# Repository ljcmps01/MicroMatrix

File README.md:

# MicroMatrix
Proyecto de matriz miniatura 8x8 controlado con STM32F051 utilizando multiplexacion

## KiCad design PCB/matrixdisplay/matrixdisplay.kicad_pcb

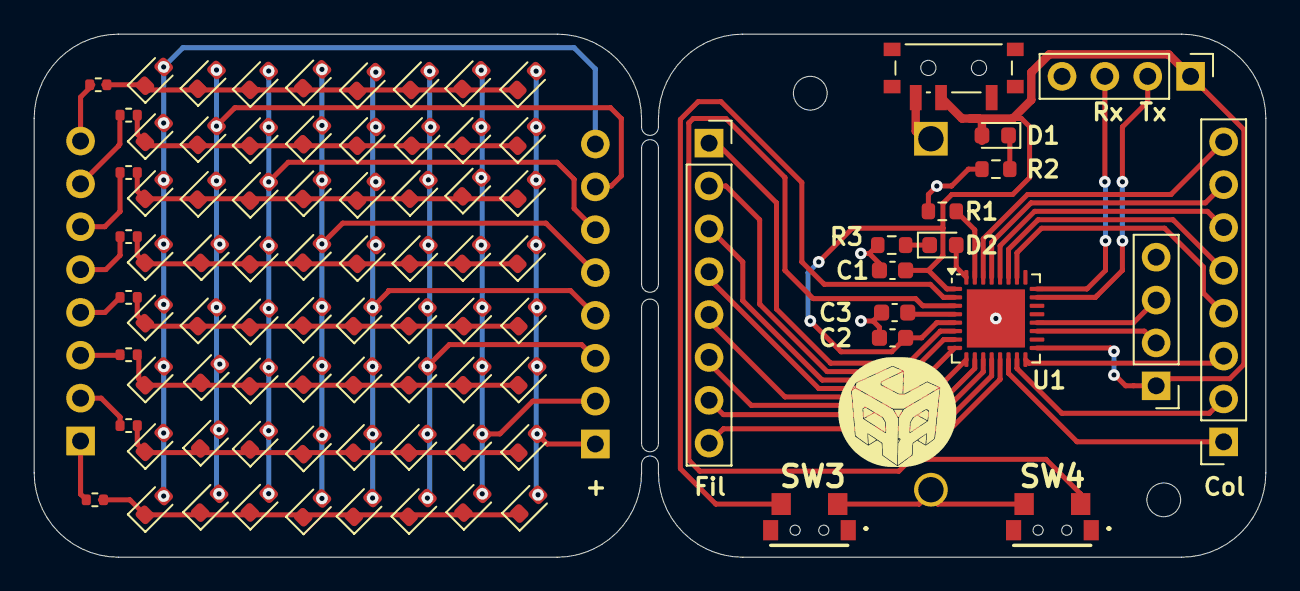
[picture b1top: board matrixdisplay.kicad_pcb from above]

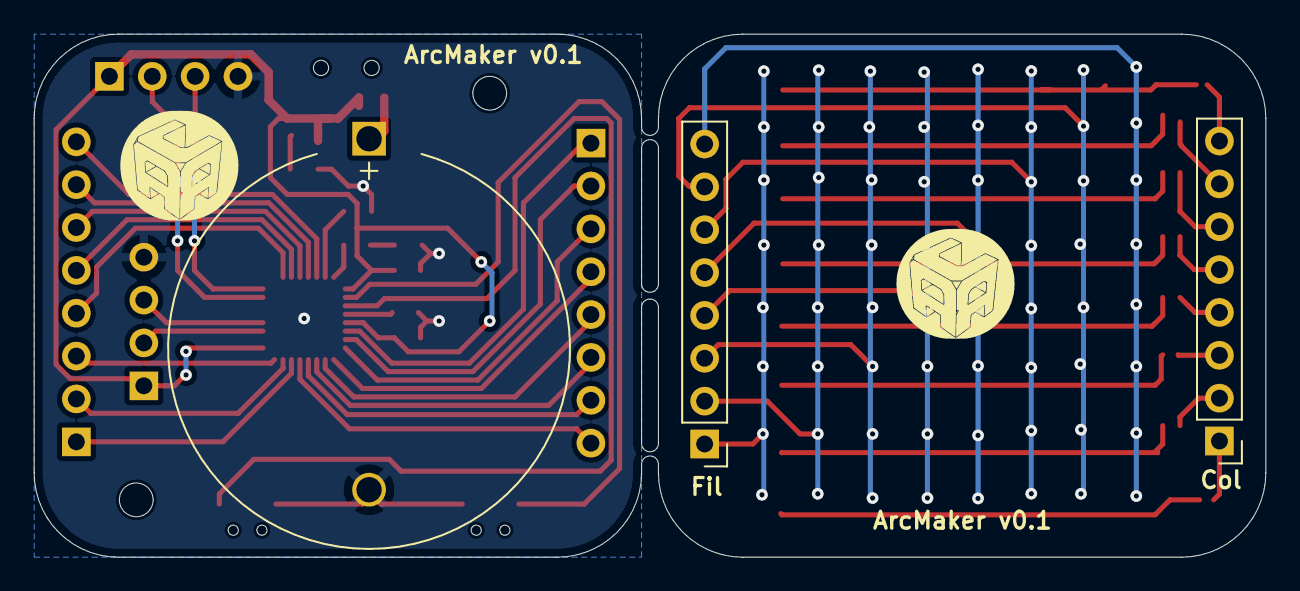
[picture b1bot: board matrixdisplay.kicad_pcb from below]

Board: 2 copper layers, 73.0 x 31.0 mm, 93 parts (3 on the bottom side), 54 nets.

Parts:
BT1: CR2032; BatteryHolder_MYOUNG_BS-07-A1BJ001_CR2032
C1, C2, C3: 100n; C_0603_1608Metric
D1, D2, D3, D4, D5, D6, D7, D8, D9, D10, D11, D12, D13, D14, D15, D16, D17, D18, D19, D20, D21, D22, D23, D24, D25, D26, D27, D28, D29, D30, D31, D32, D33, D34, D35, D36, D37, D38, D39, D40, D41, D42, D43, D44, D45, D46, D47, D48, D49, D50, D51, D52, D53, D54, D55, D56, D57, D58, D59, D60, D61, D62, D63, D64, D65, D66: LED; LED_0603_1608Metric
H1, H2: MountingHole; MountingHole_2mm
J1: FILAS; PinSocket_1x08_P2.54mm_Vertical
J2: COLUMNAS; PinSocket_1x08_P2.54mm_Vertical
J3: SWD; PinHeader_1x04_P2.54mm_Vertical
J4: USART; PinHeader_1x04_P2.54mm_Vertical
J5: FILAS; PinHeader_1x08_P2.54mm_Vertical
J6: COL; PinHeader_1x08_P2.54mm_Vertical
R1: 10k; R_0603_1608Metric
R2: 220; R_0603_1608Metric
R3: 120; R_0603_1608Metric
R4, R5, R6, R7, R8, R9, R10, R11: 220; R_0402_1005Metric
SW2: P_ON; SW_SPDT_PCM12
SW3: BT1; TS24CA
SW4: BT2; TS24CA
U1: STM32F051K8Ux; QFN-32-1EP_5x5mm_P0.5mm_EP3.45x3.45mm

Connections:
+3.3V: C1.1, C2.1, D1.2 (A), J3.1, J4.1, SW2.2 (B), U1.1 (VDD), U1.5 (VDDA), U1.17 (VDD)
GND: BT1.2 (-), C1.2, C2.2, C3.2, J3.4, J4.4, R1.1, R2.2, R3.1, SW3.2, SW4.2, U1.33 (VSS)
unnamed: BT1.1 (+), SW2.3 (C)
unnamed: D1.1 (K), R2.1
unnamed: D2.2 (A), U1.32 (PB8)
unnamed: D2.1 (K), R3.2
unnamed: D3.2 (A), D4.2 (A), D5.2 (A), D6.2 (A), D7.2 (A), D8.2 (A), D9.2 (A), D10.2 (A), J5.8
unnamed: D10.1 (K), D18.1 (K), D26.1 (K), D34.1 (K), D63.1 (K), D64.1 (K), D65.1 (K), D66.1 (K), R4.2
unnamed: D11.2 (A), D12.2 (A), D13.2 (A), D14.2 (A), D15.2 (A), D16.2 (A), D17.2 (A), D18.2 (A), J5.7
unnamed: D3.1 (K), D11.1 (K), D19.1 (K), D27.1 (K), D35.1 (K), D36.1 (K), D37.1 (K), D38.1 (K), R11.1
unnamed: D4.1 (K), D12.1 (K), D20.1 (K), D28.1 (K), D39.1 (K), D40.1 (K), D41.1 (K), D42.1 (K), R10.1
unnamed: D5.1 (K), D13.1 (K), D21.1 (K), D29.1 (K), D43.1 (K), D44.1 (K), D45.1 (K), D46.1 (K), R9.1
unnamed: D6.1 (K), D14.1 (K), D22.1 (K), D30.1 (K), D47.1 (K), D48.1 (K), D49.1 (K), D50.1 (K), R8.1
unnamed: D7.1 (K), D15.1 (K), D23.1 (K), D31.1 (K), D51.1 (K), D52.1 (K), D53.1 (K), D54.1 (K), R7.2
unnamed: D8.1 (K), D16.1 (K), D24.1 (K), D32.1 (K), D55.1 (K), D56.1 (K), D57.1 (K), D58.1 (K), R6.2
unnamed: D9.1 (K), D17.1 (K), D25.1 (K), D33.1 (K), D59.1 (K), D60.1 (K), D61.1 (K), D62.1 (K), R5.2
unnamed: D19.2 (A), D20.2 (A), D21.2 (A), D22.2 (A), D23.2 (A), D24.2 (A), D25.2 (A), D26.2 (A), J5.6
unnamed: D27.2 (A), D28.2 (A), D29.2 (A), D30.2 (A), D31.2 (A), D32.2 (A), D33.2 (A), D34.2 (A), J5.5
unnamed: D35.2 (A), D39.2 (A), D43.2 (A), D47.2 (A), D51.2 (A), D55.2 (A), D59.2 (A), D63.2 (A), J5.4
unnamed: D36.2 (A), D40.2 (A), D44.2 (A), D48.2 (A), D52.2 (A), D56.2 (A), D60.2 (A), D64.2 (A), J5.3
unnamed: D37.2 (A), D41.2 (A), D45.2 (A), D49.2 (A), D53.2 (A), D57.2 (A), D61.2 (A), D65.2 (A), J5.2
unnamed: D38.2 (A), D42.2 (A), D46.2 (A), D50.2 (A), D54.2 (A), D58.2 (A), D62.2 (A), D66.2 (A), J5.1
unnamed: J1.1, U1.6 (PA0)
unnamed: J1.2, U1.7 (PA1)
unnamed: J1.3, U1.8 (PA2)
unnamed: J1.4, U1.9 (PA3)
unnamed: J1.5, U1.10 (PA4)
unnamed: J1.6, U1.11 (PA5)
unnamed: J1.7, U1.12 (PA6)
unnamed: J1.8, U1.13 (PA7)
unnamed: J2.1, U1.14 (PB0)
unnamed: J2.2, U1.15 (PB1)
unnamed: J2.3, U1.16 (PB2)
unnamed: J2.4, U1.26 (PB3)
unnamed: J2.5, U1.27 (PB4)
unnamed: J2.6, U1.28 (PB5)
unnamed: J2.7, U1.29 (PB6)
unnamed: J2.8, U1.30 (PB7)
unnamed: J3.2, U1.23 (PA13)
unnamed: J3.3, U1.24 (PA14)
unnamed: J4.2, U1.19 (PA9)
unnamed: J4.3, U1.20 (PA10)
unnamed: J6.1, R4.1
unnamed: J6.2, R5.1
unnamed: J6.3, R6.1
unnamed: J6.4, R7.1
unnamed: J6.5, R8.2
unnamed: J6.6, R9.2
unnamed: J6.7, R10.2
unnamed: J6.8, R11.2
unnamed: R1.2, U1.31 (BOOT0)
unnamed: C3.1, U1.4 (NRST)
unnamed: SW3.1, U1.2 (PF0)
unnamed: SW4.1, U1.3 (PF1)

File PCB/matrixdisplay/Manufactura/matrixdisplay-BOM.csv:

"Reference","Value","Datasheet","Footprint","Qty","DNP"
"BT1","CR2032","~","Battery:BatteryHolder_MYOUNG_BS-07-A1BJ001_CR2032","1",""
"C1,C2,C3","100n","~","Capacitor_SMD:C_0603_1608Metric","3",""
"D1,D2,D3,D4,D5,D6,D7,D8,D9,D10,D11,D12,D13,D14,D15,D16,D17,D18,D19,D20,D21,D22,D23,D24,D25,D26,D27,D28,D29,D30,D31,D32,D33,D34,D35,D36,D37,D38,D39,D40,D41,D42,D43,D44,D45,D46,D47,D48,D49,D50,D51,D52,D53,D54,D55,D56,D57,D58,D59,D60,D61,D62,D63,D64,D65,D66","LED","~","LED_SMD:LED_0603_1608Metric","66",""
"J1,J5","FILAS","~","-- mixed values --","2",""
"J2","COLUMNAS","~","Connector_PinSocket_2.54mm:PinSocket_1x08_P2.54mm_Vertical","1",""
"J3","SWD","~","Connector_PinHeader_2.54mm:PinHeader_1x04_P2.54mm_Vertical","1",""
"J4","USART","~","Connector_PinHeader_2.54mm:PinHeader_1x04_P2.54mm_Vertical","1",""
"J6","COL","~","Connector_PinHeader_2.54mm:PinHeader_1x08_P2.54mm_Vertical","1",""
"R1","10k","~","Resistor_SMD:R_0603_1608Metric","1",""
"R2,R4,R5,R6,R7,R8,R9,R10,R11","220","~","-- mixed values --","9",""
"R3","120","~","Resistor_SMD:R_0603_1608Metric","1",""
"SW1","BOOT0","~","Button_Switch_SMD:SW_SPST_B3U-1100P","1",""
"SW2","P_ON","~","Button_Switch_SMD:SW_SPDT_PCM12","1",""
"SW3","BT1","~","Button_Switch_SMD:SW_SPST_B3U-1100P","1",""
"SW4","BT2","~","Button_Switch_SMD:SW_SPST_B3U-1100P","1",""
"U1","STM32F051K8Ux","https://www.st.com/resource/en/datasheet/stm32f051k8.pdf","Package_DFN_QFN:QFN-32-1EP_5x5mm_P0.5mm_EP3.45x3.45mm","1",""

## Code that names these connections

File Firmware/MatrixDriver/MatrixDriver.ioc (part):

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Mcu.Name=STM32F051K8Ux
Mcu.Package=UFQFPN32
Mcu.UserName=STM32F051K8Ux
PA0.GPIOParameters=GPIO_Label
PA0.GPIO_Label=FILAS
PA0.Signal=GPIO_Output
PA1.Signal=GPIO_Output
PA10.Mode=Asynchronous
PA10.Signal=USART1_RX
PA13.Mode=Serial_Wire
PA13.Signal=SYS_SWDIO
PA14.Mode=Serial_Wire
PA14.Signal=SYS_SWCLK
PA2.Signal=GPIO_Output
PA3.Signal=GPIO_Output
PA4.Signal=GPIO_Output
PA5.Signal=GPIO_Output
PA6.Signal=GPIO_Output
PA7.Signal=GPIO_Output
PA9.Mode=Asynchronous
PA9.Signal=USART1_TX
PB0.GPIOParameters=GPIO_Label
PB0.GPIO_Label=COLUMNAS
PB0.Signal=GPIO_Output
PB1.Signal=GPIO_Output
PB2.Signal=GPIO_Output
PB3.Signal=GPIO_Output
PB4.Signal=GPIO_Output
PB5.Signal=GPIO_Output
PB6.Signal=GPIO_Output
PB7.Signal=GPIO_Output
PF0-OSC_IN.GPIOParameters=GPIO_PuPd,GPIO_Label
PF0-OSC_IN.GPIO_Label=SW2
PF0-OSC_IN.GPIO_PuPd=GPIO_PULLUP
PF0-OSC_IN.Signal=GPIO_Input
PF1-OSC_OUT.GPIOParameters=GPIO_PuPd,GPIO_Label
PF1-OSC_OUT.GPIO_Label=SW3
PF1-OSC_OUT.GPIO_PuPd=GPIO_PULLUP
PF1-OSC_OUT.Signal=GPIO_Input
board=custom

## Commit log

2025-05-09 Firmware Base con multiplexado
2025-05-10 Base PCB files
2025-05-10 Deleted unwanted files
2025-05-10 Modify buttons and mounting holes
    BOOT0 was removed in favor of default boot mode
    User Buttons replaced to horizontal aligment for easier access
    Mounting Holes changed to M2 instead of M3 standard
2025-05-10 Added prl file to gitignore
2025-05-10 Added images for the board
2025-05-10 carpeta de recursos movida
2025-05-11 feat(fw): Crea la estructura de la matriz con constructor e inicializador
2025-05-12 feat(fw): animacion de desplazamiento horizontal y vertical con bucle feat(fw): implementacion basica de intervalos fix(git): tipo en gitignore
2025-05-12 fix(git): gitignore para carpeta firmware
2025-05-17 mod(fw): actualiza el .ioc y regenera el codigo para la placa de desarrollo
2025-05-18 feat(fw): migracion a vector interno de estructura para imprimir en display
2025-05-18 fix(fw): definicion de matriz de escritura
2025-05-18 fix(fw): remueve completamente las variables de prueba y se crea la matriz de numeros para tener valores de prueba de impresion en pantalla
2025-05-18 feat(fw): agrega funcion de espejado horizontal
2025-05-19 feat(fw): programa prueba de contador, con funcion en botones
2025-05-19 fix(fw): correccion col encendida
2025-05-20 fix (pcb): Correcion serigrafia SWD
2025-05-20 feat (fw): Agrega funcion de espejado vertical
2025-05-21 feat(fw):Agrega archivo de fuente numerica
2025-05-25 Fix (fw): Arregla funcion de multiplexado para el estado inicial
2025-05-26 feat(fw): Agrega funcion y parametro de rotacion en matriz
2025-06-10 fix(repo): actualiza git ignore para abstraer driver matrix
2025-06-23 fix(fw): corrige funcion de rotacion y elimina depencias innecesarias
